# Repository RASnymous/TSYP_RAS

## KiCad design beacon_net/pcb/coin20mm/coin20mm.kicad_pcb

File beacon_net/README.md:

# Living Map Beacon Network (LMB2)

The radio part of the TSYP14 Living Map: the beacons the Writer drops, the LoRa gossip network between them, and the gateway that feeds the Command Post.

* **44-byte record** per beacon: id, kind, GPS position ± error, severity, confidence, next-hop vector (the way out), timestamp, TTL, confidence half-life (gas fades in minutes, an obstruction lasts days)
* **LoRa 868 MHz** (SF9, 288 ms per frame), **HMAC-SHA256** (64-bit tag, per-mission key)
* **Gossip replication**: own announce, reactive relay with route-aware suppression and passive acks, anti-entropy, pull digests. A crushed beacon's record survives in its neighbours, and the Command Post is told the beacon is lost.
* Same portable C core in the **ESP32 firmware**, the **gateway**, the **network simulator** and (mirrored byte-for-byte) **Python**

Read **[ARCHITECTURE.md](ARCHITECTURE.md)** for the full design, security analysis, radio budget and test results.

## Quick start

```bash
cd host
make                 # bptool + bpsim
./bptool example     # the brief's victim record -> 44-byte frame
./bpsim              # 60-min mission, 14 beacons, beacon loss, attacker -> report + 13 checks
make test            # C <-> Python <-> firmware cross-checks
make matrix          # 42 stress scenarios
```

Live on the dashboard (from `../command_post`, run `npm start` first):

```bash
./bpsim --speed 20 | python3 ../python/beaconnet/gateway_bridge.py --stdin --server http://localhost:3000
```

Three gateways through the Outside Network Area (2-of-3 vote, robot positioning, LTE/satellite uplink, briefings): see `../ona/README.md`.

```bash
cd ../../ona && ../beacon_net/host/bpsim --gateways 3 --speed 20 | python3 -m ona --stdin --config ona_config_bpsim.json
```

Windows: everything except ROS runs natively; open `windows/README.md` (double-click launchers, prebuilt .exe).

Hardware: `firmware/beacon_node` and `firmware/gateway_node` (ESP32 + SX1276, Arduino IDE or PlatformIO). The library is `lib/BeaconProto`. Provisioning and the serial commands are in ARCHITECTURE.md §9.

Writer (ROS 2): `python3 ros/beacon_record_node.py --ros-args -p dashboard:=http://10.0.2.2:3000`

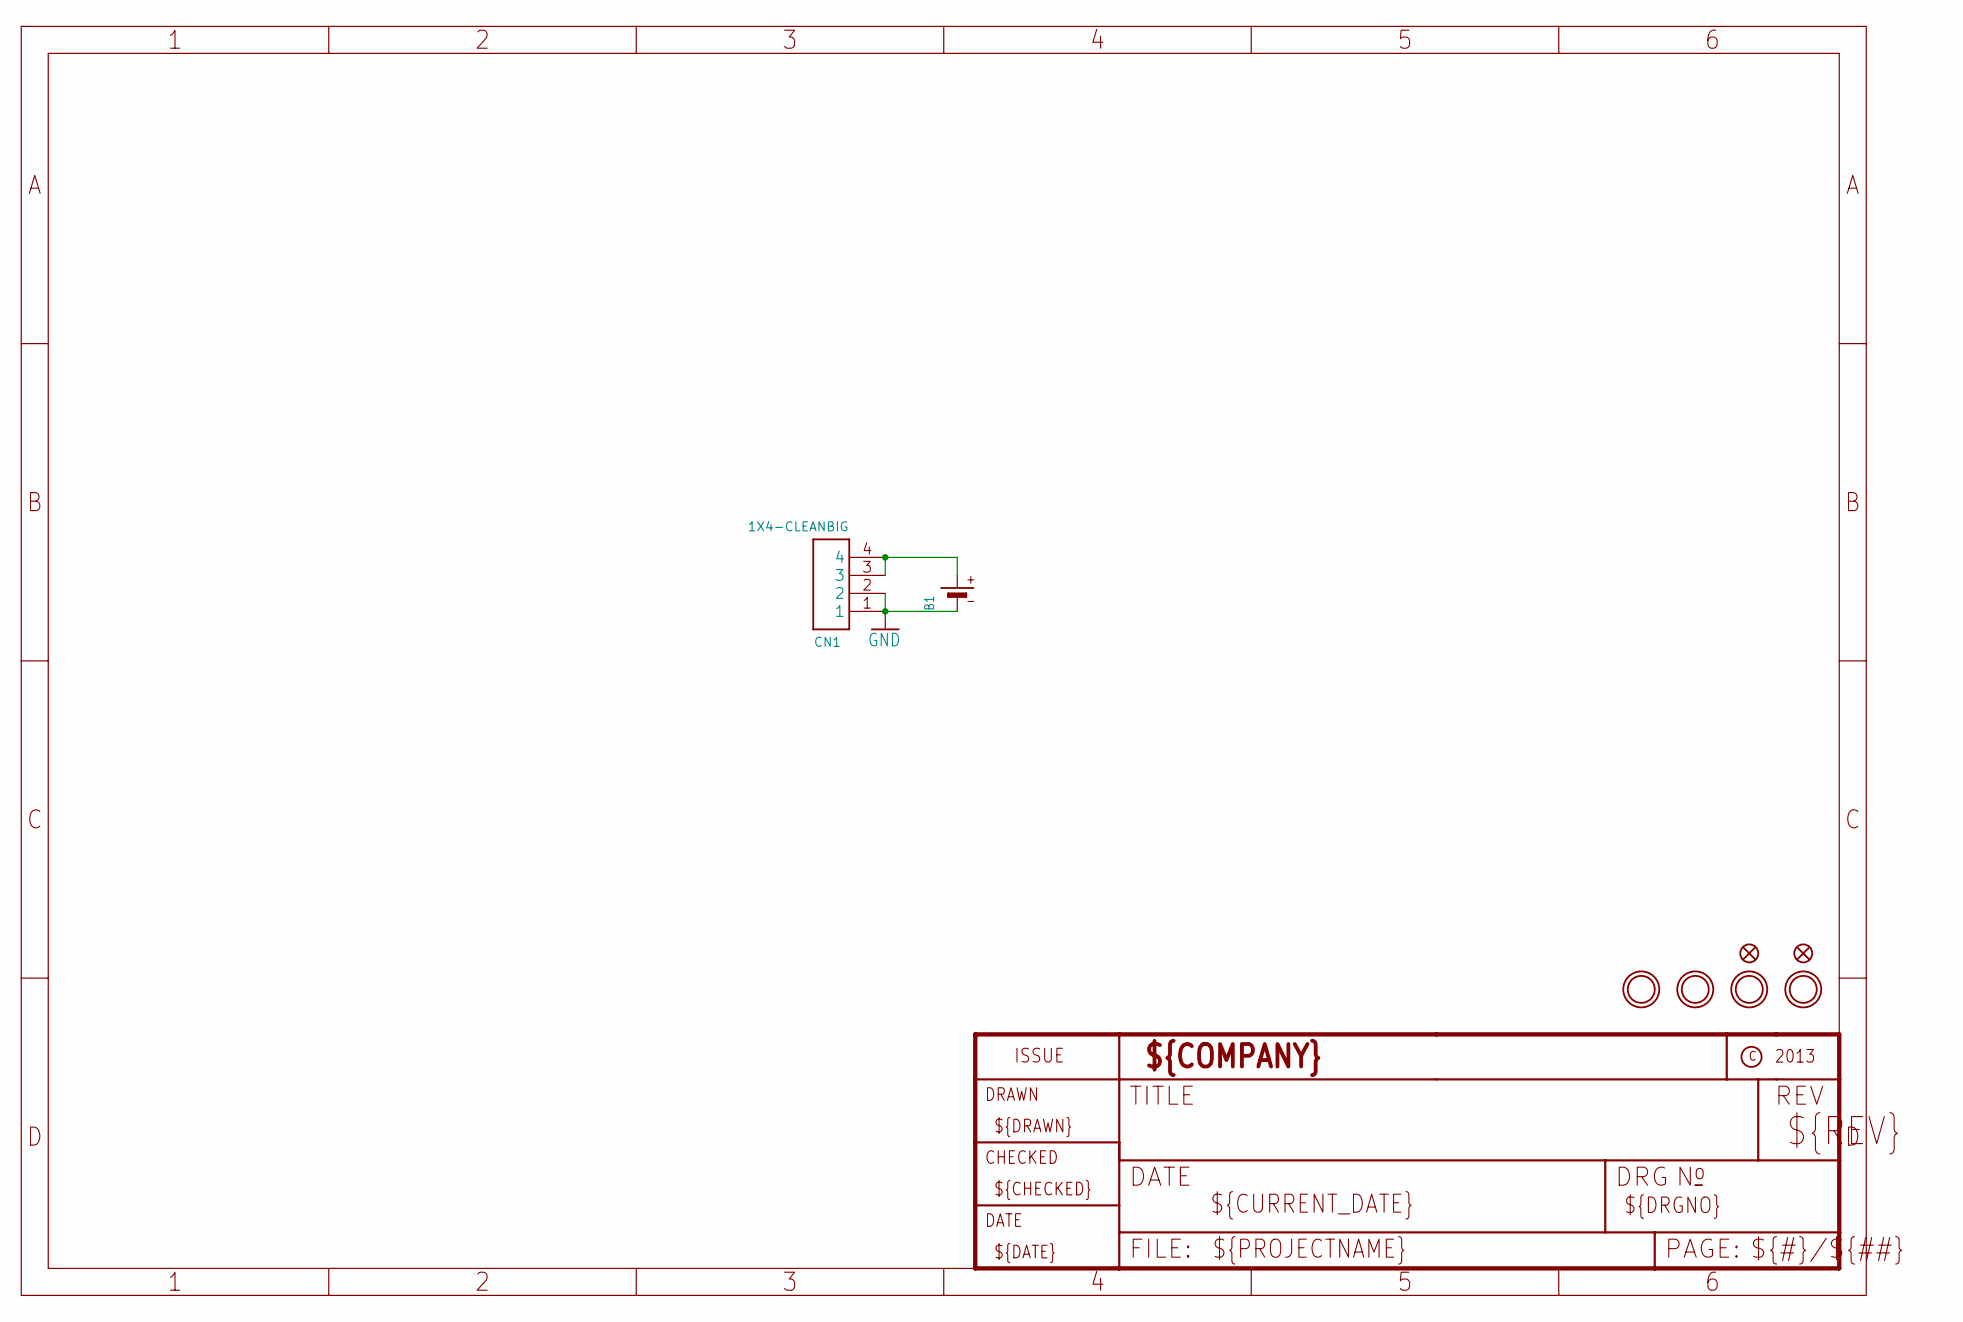
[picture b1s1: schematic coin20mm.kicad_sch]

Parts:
B1: BATTERYCR2032_BAT-HLD-001; CR2032_SMT_BAT-HLD-001
CN1: 1X4-CLEANBIG; 1X04-CLEANBIG
FID1, FID2: FIDUCIAL""; FIDUCIAL_1MM
U$1, U$2, U$3, U$5: MOUNTINGHOLE2.5; MOUNTINGHOLE_2.5_PLATED

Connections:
3V: B1.+$1 (+), B1.+$2 (+), CN1.3, CN1.4
GND: B1.-, CN1.1, CN1.2

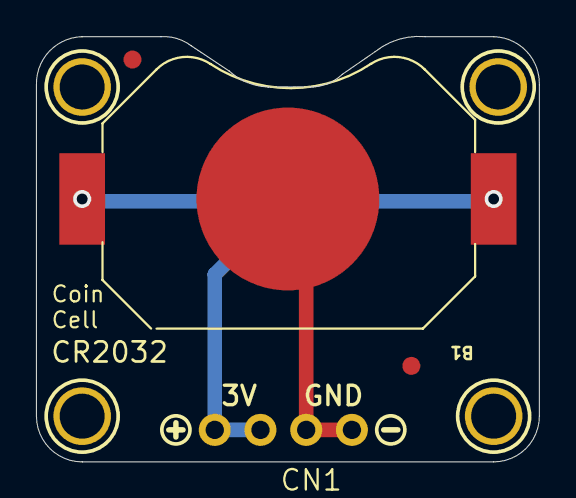
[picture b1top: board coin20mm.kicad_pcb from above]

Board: 2 copper layers, 27.9 x 23.6 mm, 10 parts (0 on the bottom side), 2 nets.

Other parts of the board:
U$6: SYMBOL_PLUS
U$7: SYMBOL_MINUS

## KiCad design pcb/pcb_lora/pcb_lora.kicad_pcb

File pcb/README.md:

# PCB — Radio Beacon

This folder contains the **PCB design and hardware documentation** for the radio beacons used in the project's resilient communication system.

## Context

In disaster response, underground exploration, and hazardous inspections, robots may operate without GPS or communication networks.

The system uses small **LoRa radio beacons** to store and relay critical mission information:

```text
Robot 1 → Beacon → Robot 2
```

A first robot can leave information at a location, allowing a second robot to retrieve it and continue the mission without starting from zero.

## PCB Role

The PCB provides the hardware platform for the beacon, including:

* Microcontroller
* LoRa communication module
* Power supply / battery interface
* Supporting electronic components

The beacon is designed to be **compact, low-power, and suitable for deployment in constrained environments**.

## Images

### PCB Size Reference

### LoRa Module

## Communication

The beacon uses **LoRa** for long-range, low-power communication. Beacon messages can contain information such as:

* Beacon ID
* Position
* Event type
* Severity / confidence
* Timestamp
* TTL

The PCB is part of the larger **autonomous robot resilient-communication system**.

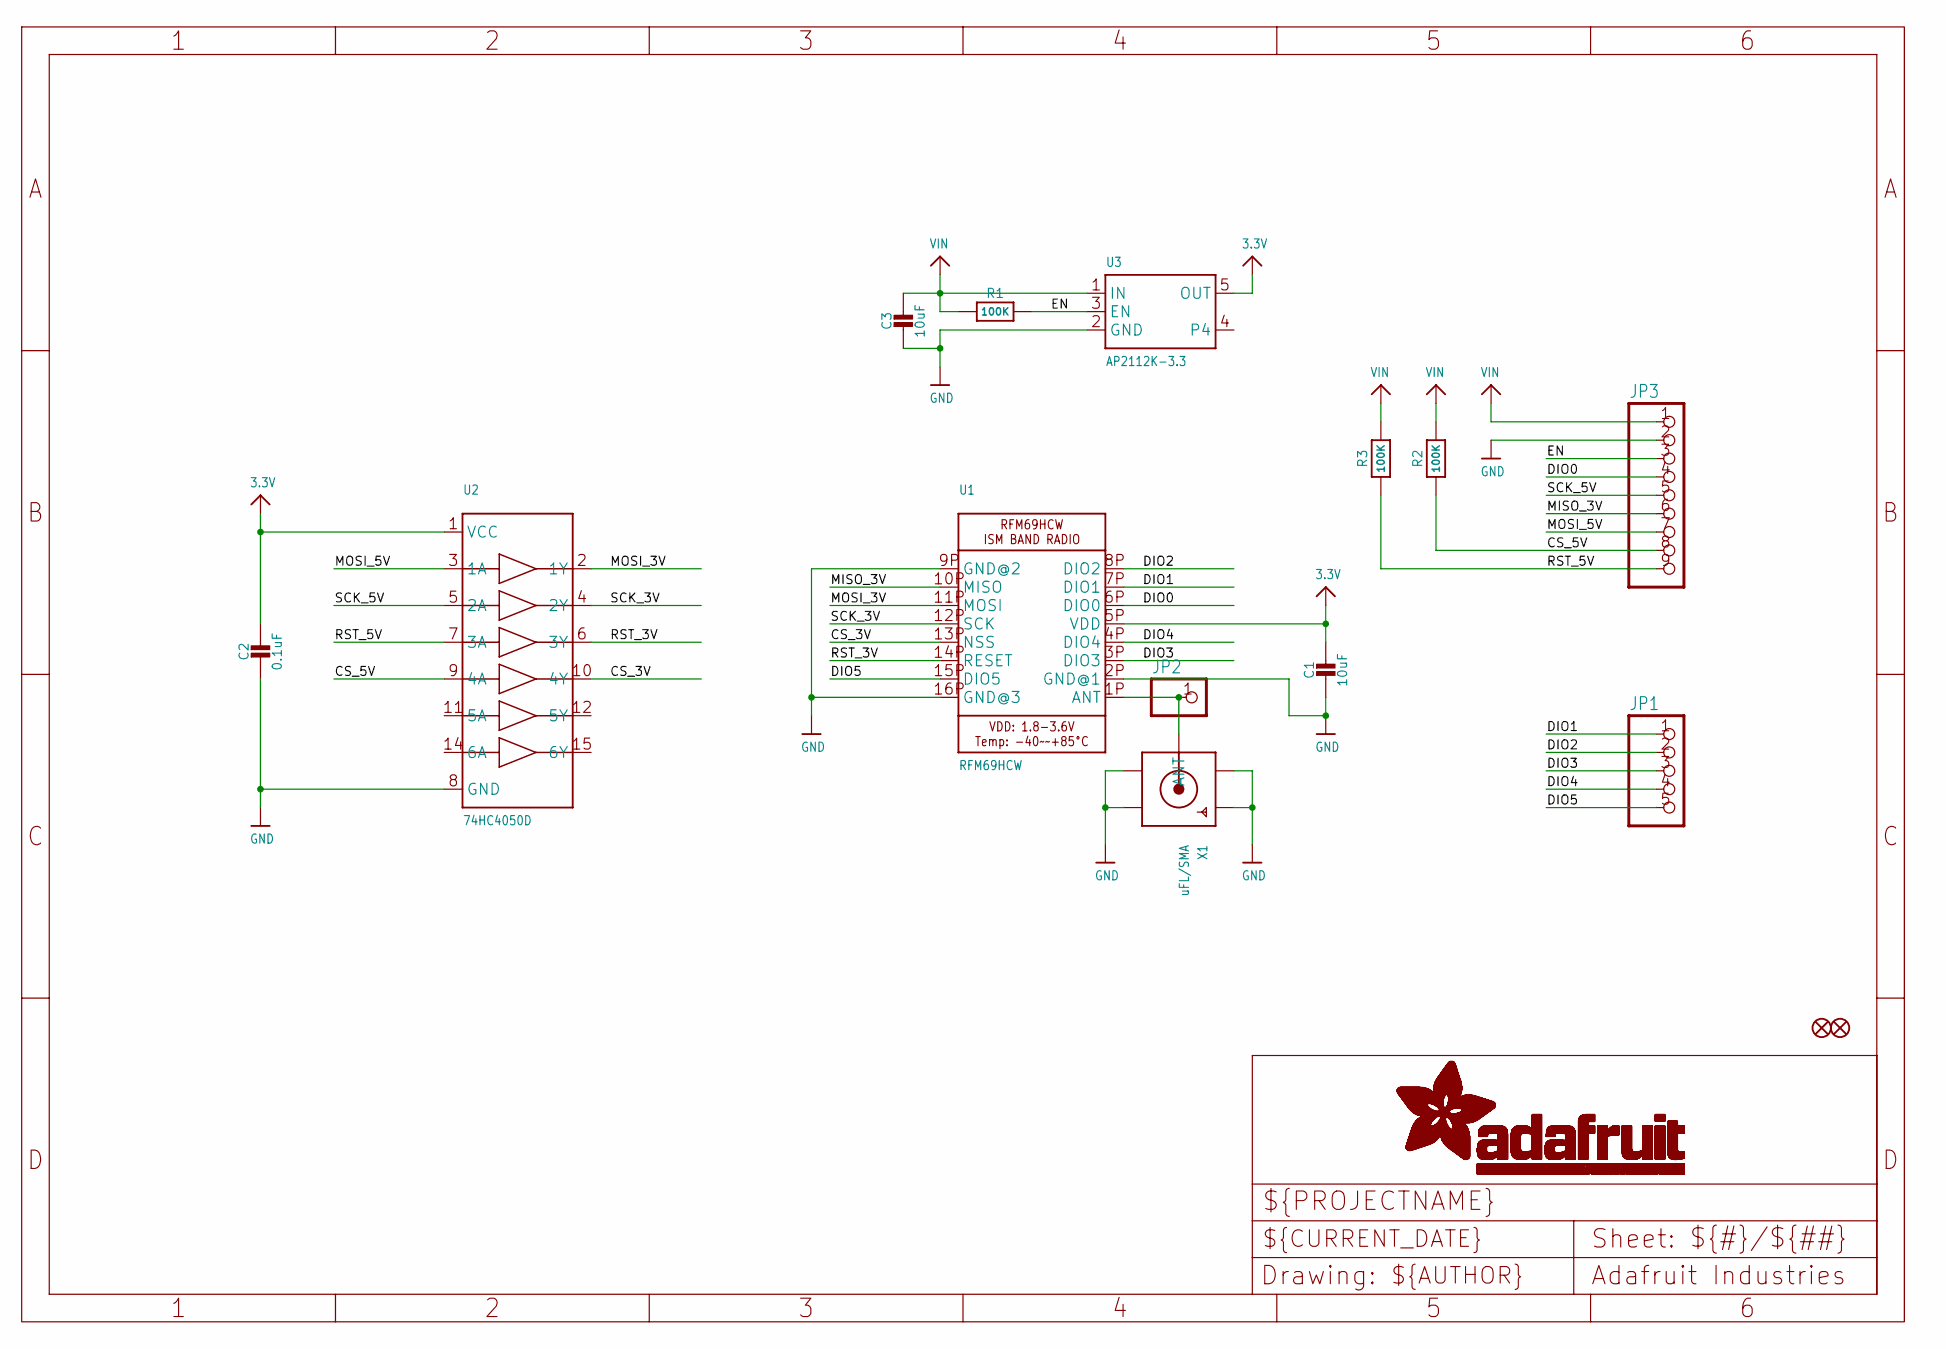
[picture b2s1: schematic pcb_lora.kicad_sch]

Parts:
C1, C3: 10uF; 0805-NO
C2: 0.1uF; 0805-NO
FID1, FID2: FIDUCIAL""; FIDUCIAL_1MM
JP1: HEADER-1X570MIL; 1X05_ROUND_70
JP2: HEADER-1X1ROUND; 1X01_ROUND
JP3: HEADER-1X970MIL; 1X09_ROUND_70
R1, R2, R3: 100K; 0805-NO
U1: RFM69HCW; RFMHCW_SMT
U2: 74HC4050D; TSSOP16
U3: AP2112K-3.3; SOT23-5
X1: uFL/SMA; SMA_EDGELAUNCH_UFL

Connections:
3.3V: C1.1, C2.1, U1.5P (VDD), U2.1 (VCC), U3.5 (OUT)
CS_3V: U1.13P (NSS), U2.10 (4Y)
CS_5V: JP3.8, R2.1, U2.9 (4A)
DIO0: JP3.4, U1.6P (DIO0)
DIO1: JP1.1, U1.7P (DIO1)
DIO2: JP1.2, U1.8P (DIO2)
DIO3: JP1.3, U1.3P (DIO3)
DIO4: JP1.4, U1.4P (DIO4)
DIO5: JP1.5, U1.15P (DIO5)
EN: JP3.3, R1.2, U3.3 (EN)
GND: C1.2, C2.2, C3.2, JP3.2, U1.2P (GND@1), U1.9P (GND@2), U1.16P (GND@3), U2.8 (GND), U3.2 (GND), X1.GND@1 (GND1), X1.GND@2 (GND2), X1.GND@3 (GND3), X1.GND@4 (GND4)
MISO_3V: JP3.6, U1.10P (MISO)
MOSI_3V: U1.11P (MOSI), U2.2 (1Y)
MOSI_5V: JP3.7, U2.3 (1A)
unnamed: JP2.1, U1.1P (ANT), X1.P (ANT)
RST_3V: U1.14P (RESET), U2.6 (3Y)
RST_5V: JP3.9, R3.1, U2.7 (3A)
SCK_3V: U1.12P (SCK), U2.4 (2Y)
SCK_5V: JP3.5, U2.5 (2A)
VIN: C3.1, JP3.1, R1.1, R2.2, R3.2, U3.1 (IN)

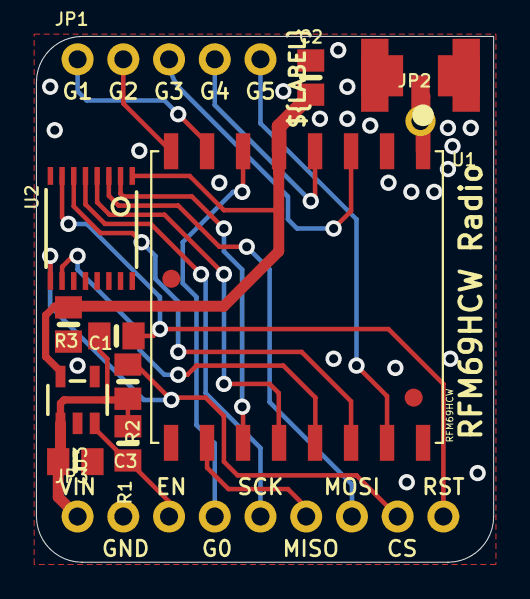
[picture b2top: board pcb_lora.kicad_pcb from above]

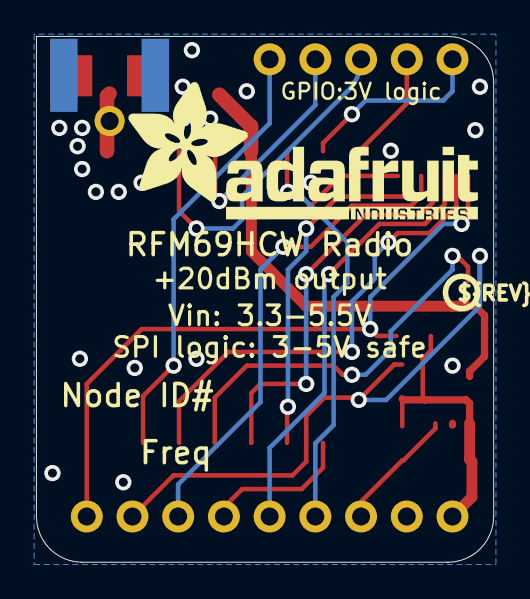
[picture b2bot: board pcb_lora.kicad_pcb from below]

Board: 2 copper layers, 25.4 x 29.2 mm, 17 parts (2 on the bottom side), 20 nets.

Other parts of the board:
U$14: PCBFEAT-REV-040
U$19: ADAFRUIT_TEXT_20MM
